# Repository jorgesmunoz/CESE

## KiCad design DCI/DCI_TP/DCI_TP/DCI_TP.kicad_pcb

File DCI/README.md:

# DCI
Repositorio de la materia DCI

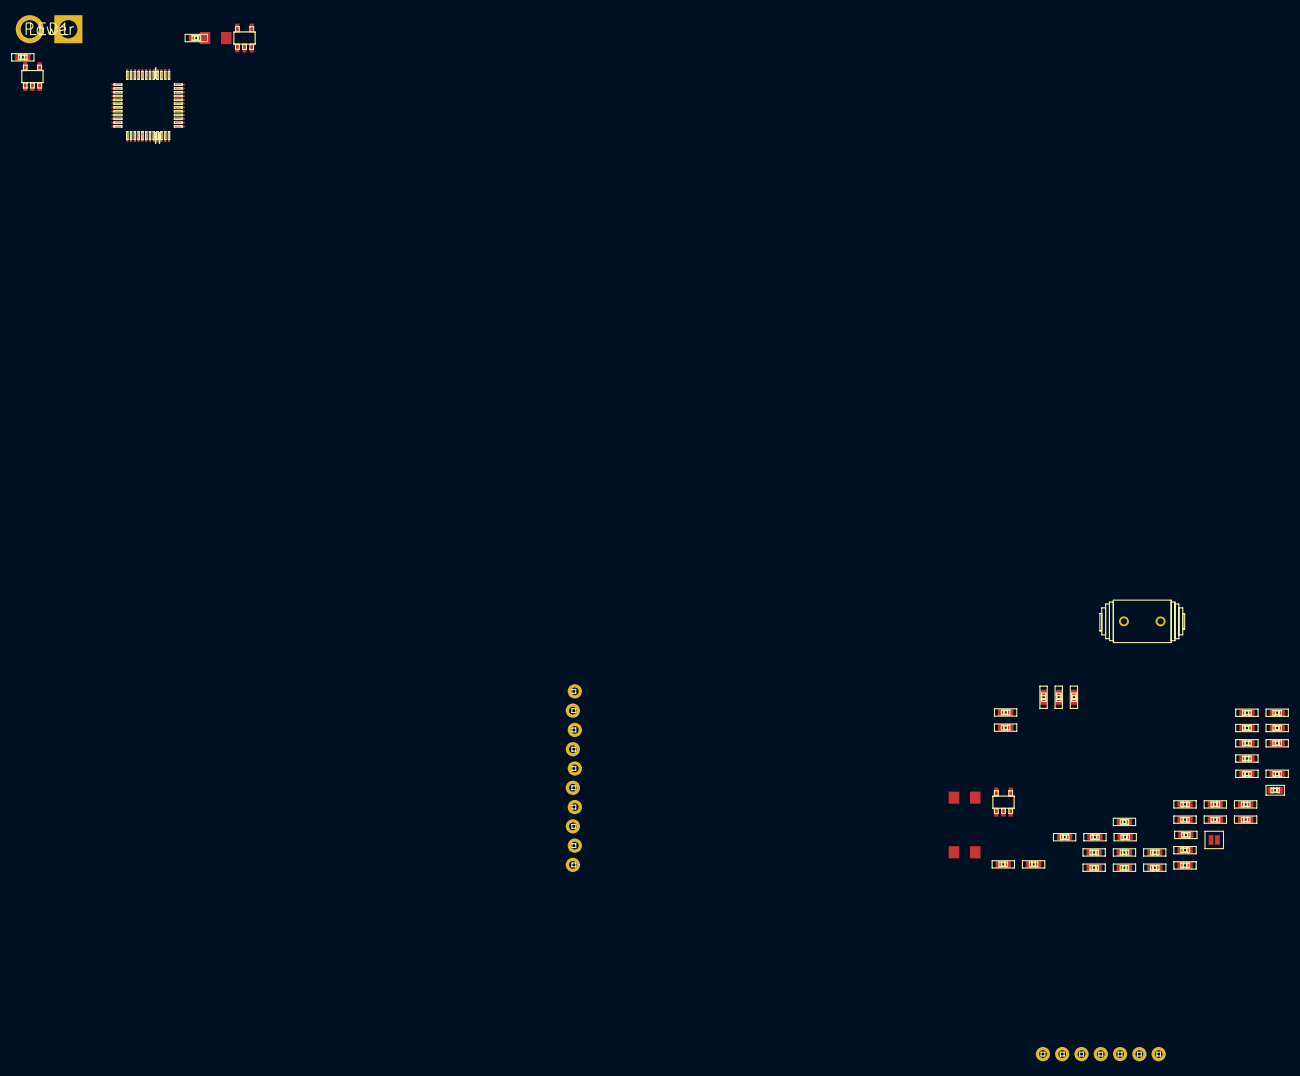
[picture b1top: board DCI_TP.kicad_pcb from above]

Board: 2 copper layers, 50 parts (0 on the bottom side), 36 nets, no tracks yet.

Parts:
C1, C2, C3, C7, C11, C12, C15, C16, C17, C18: 100nF; 0402-CAP
C4, C5, C6: 10uF; EIA3216
C8, C9, C10, C22: 0.1uF; 0402-CAP
C13, C14: 18pF; 0402-CAP
C19, C21, C23, C24: 10nF; 0402-CAP
C20: 47nF; 0402-CAP
JP1: M10; 1X10_LOCK
JP3: M07; 1X07
JP4: JUMPER; SJ_2S
LED1: Power; LED10MM
Q1: 12.288Mhz; HC49U-V
R1: 330; 0402-RES
R2, R3, R4, R5, R7, R8, R9, R10, R16, R17: 100k; 0402-RES
R6: 1M; 0402-RES
R11, R13: 20; 0402-RES
R12: 10; 0402-RES
R14, R15: 470; 0402-RES
U1, U2, U3: V_REG_LDOSMD; SOT23-5
VS1053: VS1033_1053SMD; LQFP-48

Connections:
/AGND: C1.2, C2.2, C3.2, C5.C, C9.2, C19.2, C20.2, C21.2, C22.2, C23.2, C24.2, JP3.7, JP4.2, U2.3, VS1053.37, VS1053.40, VS1053.41, VS1053.47
/AVDD: C1.1, C2.1, C3.1, C5.A, C9.1, U2.5, VS1053.38, VS1053.43, VS1053.45
/CS: JP1.10, VS1053.23
/CVDD: C6.A, C7.1, C10.1, C11.1, C12.1, C15.1, U3.5, VS1053.5, VS1053.7, VS1053.24, VS1053.31
/GBUF: JP1.3, R12.1, VS1053.42
/GPIO0: JP1.6, R17.1, VS1053.33
/GPIO1: JP1.5, R16.1, VS1053.34
/GPIO2: R4.1, VS1053.9
/GPIO3: R3.1, VS1053.10
/GPIO4: JP3.6, R10.1, VS1053.36
/GPIO5: JP3.5, R9.1, VS1053.25
/GPIO6: JP3.2, R7.1, VS1053.11
/GPIO7: JP3.3, R8.1, VS1053.12
/IOVDD: C4.A, C8.1, C16.1, C17.1, C18.1, R2.1, R5.1, U1.5, VS1053.6, VS1053.14, VS1053.19, VS1053.32
/LEFT: JP1.4, R13.1, VS1053.46
/LINEIN: C23.1, JP3.1, R15.2
/MICP: C24.1, R14.2
/PWR_FLAG: VS1053.4, VS1053.16, VS1053.20, VS1053.21, VS1053.22, VS1053.35
/RESET: R2.2, VS1053.3
/RIGHT: JP1.2, R11.1, VS1053.39
/RX: R5.2, VS1053.26
/SCLK: JP1.9, VS1053.28
/SI: JP1.8, VS1053.29
/SO: JP1.7, VS1053.30
/VCC: JP1.1, R1.1, U1.1, U1.2, U2.1, U2.2, U3.1, U3.2
/VCO: JP3.4, VS1053.15
GND: C4.C, C6.C, C7.2, C8.2, C10.2, C11.2, C12.2, C13.2, C14.2, C15.2, C16.2, C17.2, C18.2, JP4.1, LED1.C, R3.2, R4.2, R7.2, R8.2, R9.2, R10.2, R16.2, R17.2, U1.3, U3.3
unnamed: C13.1, Q1.1, R6.1, VS1053.18
unnamed: C14.1, Q1.2, R6.2, VS1053.17
unnamed: C19.1, R11.2
unnamed: C20.1, R12.2
unnamed: C21.1, R13.2
unnamed: C22.1, VS1053.44
unnamed: LED1.A, R1.2
unnamed: R14.1, VS1053.1
unnamed: R15.1, VS1053.48

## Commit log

2020-08-31 "First commit DASO"
2020-08-31 "Commit de prueba"
2020-08-31 "Commit clase 1"
2020-09-05 First commit CLP
2020-09-07 "New commit"
2020-09-07 "Commit clase 2 DASO"
2020-09-07 "Commit DASO clase 2"
2020-09-10 Commit RTOSI
2020-09-11 Repositorio DCI
2020-09-20 Commit CLP
2020-09-27 Commit DASO
2020-10-31 Commit RTOS2
